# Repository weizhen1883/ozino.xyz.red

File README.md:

# ozino.xyz.red
ozino.xyz.red uses a msp430g2553 16bit MCU, and can be programed through USB.

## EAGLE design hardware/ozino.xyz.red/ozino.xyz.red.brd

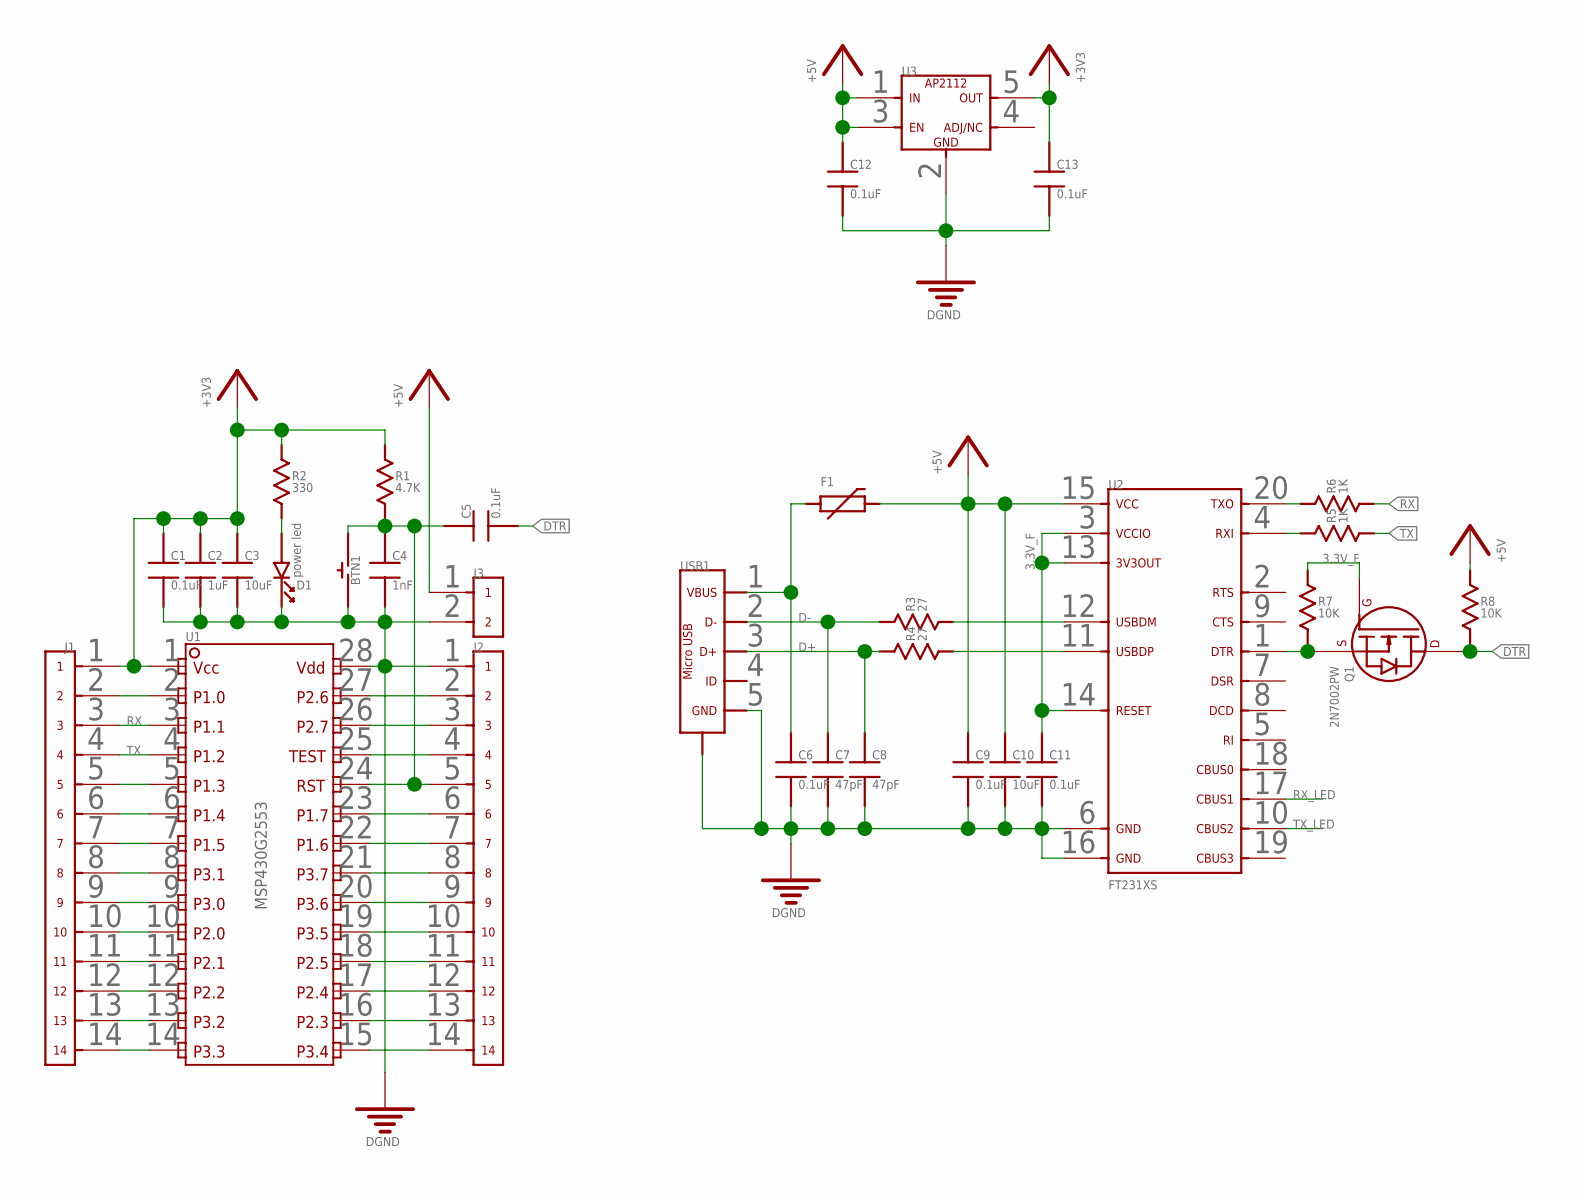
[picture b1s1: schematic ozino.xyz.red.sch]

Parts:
BTN1: BTN_NORMAL_OFF_6_3.5_SMD; BTN_6_3.5_SMD
C1, C5, C6, C9, C11, C12, C13: 0.1uF; 0402
C2: 1uF; 0402
C3, C10: 10uF; 0402
C4: 1nF; 0402
C7, C8: 47pF; 0402
D1: power led; 0805DIODE
F1: PTC_0805; 0805
J1, J2: 14PIN_HEADER_PITCH2.54MM_TH
J3: 2PIN_HEADER_PITCH2.54MM_TH
Q1: 2N7002PW; SOT323(SC-70)
R1: 4.7K; 0402
R2: 330; 0805
R3, R4: 27; 0402
R5, R6: 1K; 0402
R7, R8: 10K; 0402
U1: MSP430G2553_24IO_28PIN_TSSOP; TSSOP-28
U2: FT231XS_SSOP20; SSOP-20
U3: AP2112K_SOT-23-5; SOT-23-5
USB1: USB-2.0-MICRO_SMD_SMD; MICRO-USB-B-SMD-SMD

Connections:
3.3V_F: C11.1, Q1.1 (G), R7.1, U2.3, U2.13, U2.14
+3V3: C1.1, C2.1, C3.1, C13.1, J1.1, R1.1, R2.1, U1.1, U3.5
+5V: C9.1, C10.1, C12.1, F1.2, J3.1, R8.1, U2.15, U3.1, U3.3
D+: C8.1, R4.1, USB1.3 (D+)
D-: C7.1, R3.1, USB1.2 (D-)
DGND: BTN1.1, C1.2, C2.2, C3.2, C4.2, C6.2, C7.2, C8.2, C9.2, C10.2, C11.2, C12.2, C13.2, D1.1 (K), J2.1, J3.2, U1.28, U2.16, U3.2, USB1.5 (GND), USB1.M1 (SHIELD), USB1.M2 (SHIELD), USB1.M3 (SHIELD), USB1.M4 (SHIELD), USB1.S1 (SHIELD), USB1.S2 (SHIELD)
DTR: C5.2, Q1.3 (D), R8.2
unnamed: R3.2, U2.12
unnamed: D1.2 (A), R2.2
unnamed: R4.2, U2.11
unnamed: C6.1, F1.1, USB1.1 (VBUS)
unnamed: R6.1, U2.20
unnamed: R5.1, U2.4
unnamed: Q1.2 (S), R7.2, U2.1
P1.0: J1.2, U1.2
P1.3: J1.5, U1.5
P1.4: J1.6, U1.6
P1.5: J1.7, U1.7
P1.7: J2.6, U1.23
P2.0: J1.10, U1.10
P2.1: J1.11, U1.11
P2.2: J1.12, U1.12
P2.3: J2.13, U1.16
P2.4: J2.12, U1.17
P2.5: J2.11, U1.18
P2.6: J2.2, U1.27
P2.7: J2.3, U1.26
P3.0: J1.9, U1.9
P3.1: J1.8, U1.8
P3.2: J1.13, U1.13
P3.3: J1.14, U1.14
P3.4: J2.14, U1.15
P3.5: J2.10, U1.19
P3.6: J2.9, U1.20
P3.7: J2.8, U1.21
P`.6: J2.7, U1.22
RST: BTN1.2, C4.1, C5.1, J2.5, R1.2, U1.24
RX: J1.3, R6.2, U1.3
RX_LED: U2.17
TEST: J2.4, U1.25
TX: J1.4, R5.2, U1.4
TX_LED: U2.10

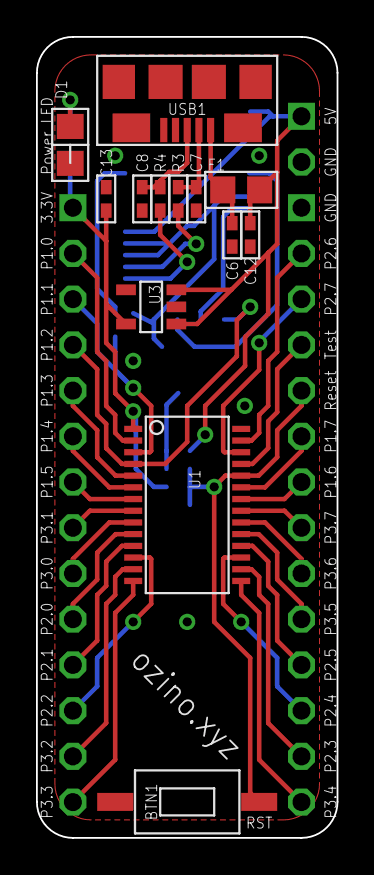
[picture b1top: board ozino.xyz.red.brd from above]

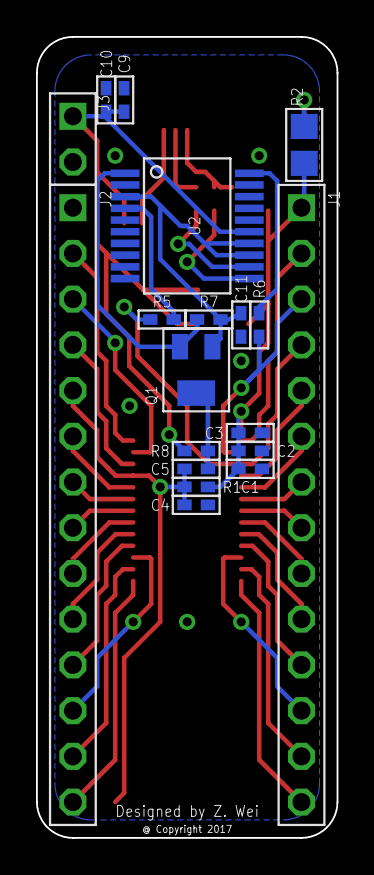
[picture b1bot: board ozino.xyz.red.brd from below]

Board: 2 copper layers, 16.7 x 44.5 mm, 32 parts (19 on the bottom side), 40 nets.

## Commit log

2017-09-10 V1 updated

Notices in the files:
hardware/ozino.xyz.red/ozino.xyz.red.brd:
@ Copyright 2017
